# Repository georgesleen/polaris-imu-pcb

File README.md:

# Polaris IMU PCB

## Images

## Drawings

## Ordering

When ordering this PCB, please tag the commit that you used and create a release on GitHub with the appropriate revision number.

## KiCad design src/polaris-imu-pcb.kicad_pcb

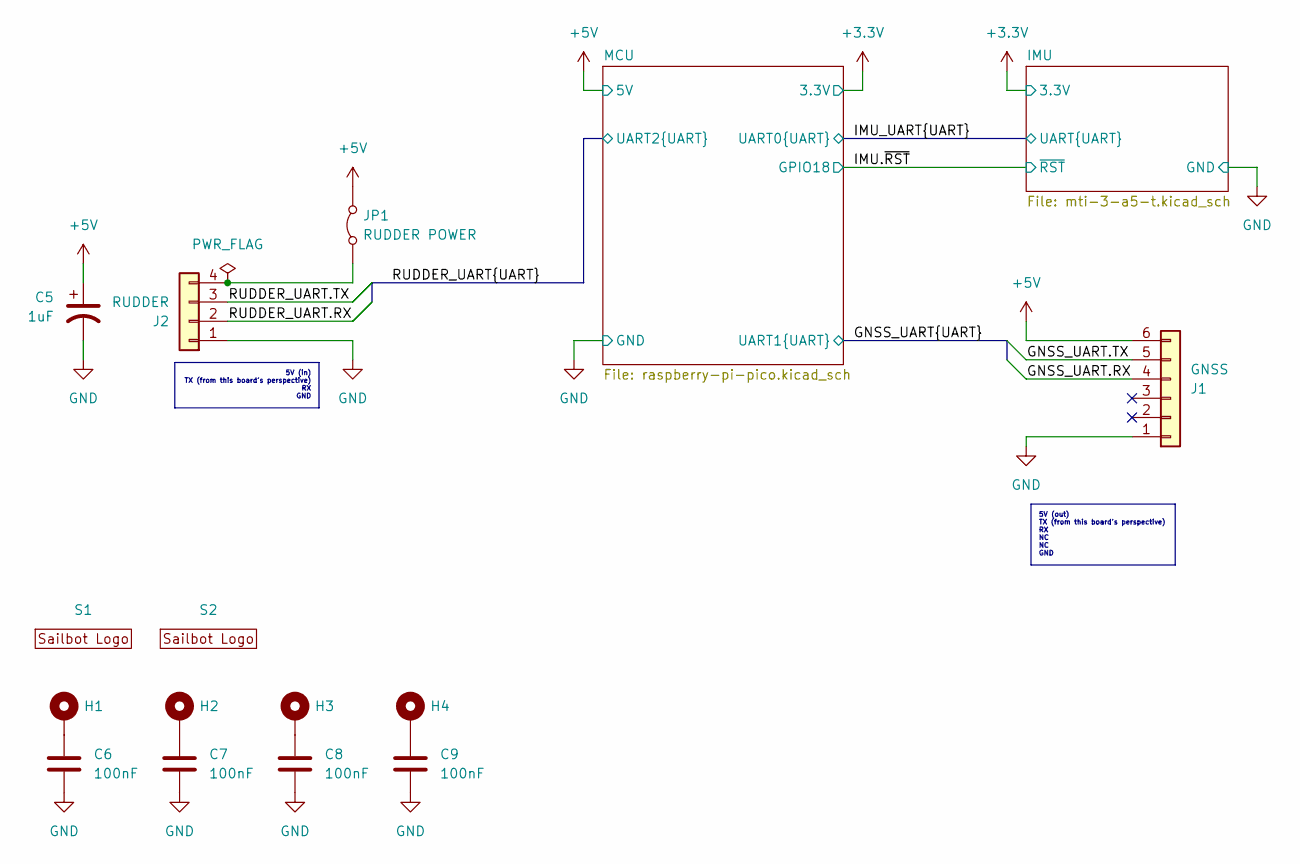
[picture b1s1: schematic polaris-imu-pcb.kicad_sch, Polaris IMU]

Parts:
C5: 1uF; CP_Radial_D5.0mm_P2.00mm
C6, C7, C8, C9: 100nF; C_Disc_D3.0mm_W2.0mm_P2.50mm
H1, H2, H3, H4: MountingHole_Pad; MountingHole_3.2mm_M3_Pad
J1: GNSS; JST_XH_S6B-XH-A-1_1x06_P2.50mm_Horizontal; MPN S6B-XH-A-1(LF)(SN); LCSC ID C265069
J2: RUDDER; JST_XH_S4B-XH-A-1_1x04_P2.50mm_Horizontal; MPN S4B-XH-A-1(LF)(SN); LCSC ID C163037
JP1: RUDDER POWER; TestPoint_2Pads_Pitch2.54mm_Drill0.8mm
S1: Logo; UBC_Sailbot_Logo_Silk
S2: Logo; UBC_Sailbot_Logo_Huge

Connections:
/+5V: C5.1, J1.6, JP1.2 (B); also elsewhere on the board
/GND: C5.2, C6.2, C7.2, C8.2, C9.2, J1.1, J2.1; also elsewhere on the board
/GNSS_UART.RX: J1.4; also elsewhere on the board
/GNSS_UART.TX: J1.5; also elsewhere on the board
/RUDDER_UART.RX: J2.2; also elsewhere on the board
/RUDDER_UART.TX: J2.3; also elsewhere on the board
unnamed: C6.1, H1.1 (1_1)
unnamed: C7.1, H2.1 (1_1)
unnamed: C8.1, H3.1 (1_1)
unnamed: C9.1, H4.1 (1_1)
unnamed: J2.4, JP1.1 (A)

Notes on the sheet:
5V (out) TX (from this board's perspective) RX NC NC GND
5V (in) TX (from this board's perspective) RX GND

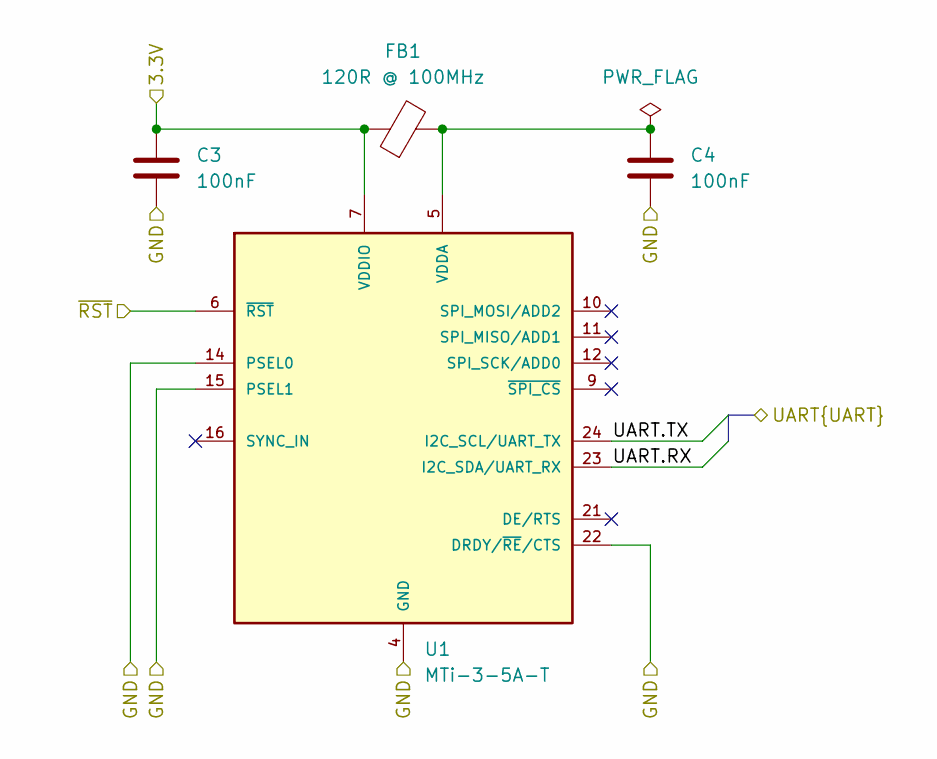
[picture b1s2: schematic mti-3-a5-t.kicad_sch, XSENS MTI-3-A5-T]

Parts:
C3, C4: 100nF; C_Disc_D3.0mm_W2.0mm_P2.50mm
FB1: 120R @ 100MHz; L_0603_1608Metric; MPN BLM18KG121TN1D; LCSC ID C85831
U1: MTi-3-5A-T; PLCC-28-AT; MPN MTi-3-5A-T

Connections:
/+3.3V: C3.1, FB1.1, U1.7 (VDDIO); also elsewhere on the board
/GND: C3.2, C4.2, U1.4 (GND), U1.8 (GND), U1.13 (GND), U1.14 (PSEL0), U1.15 (PSEL1), U1.22 (DRDY/~RE/CTS), U1.25 (GND); also elsewhere on the board
/IMU.~RST: U1.6 (~RST); also elsewhere on the board
/IMU_UART.RX: U1.23 (I2C_SDA/UART_RX); also elsewhere on the board
/IMU_UART.TX: U1.24 (I2C_SCL/UART_TX); also elsewhere on the board
unnamed: C4.1, FB1.2, U1.5 (VDDA)

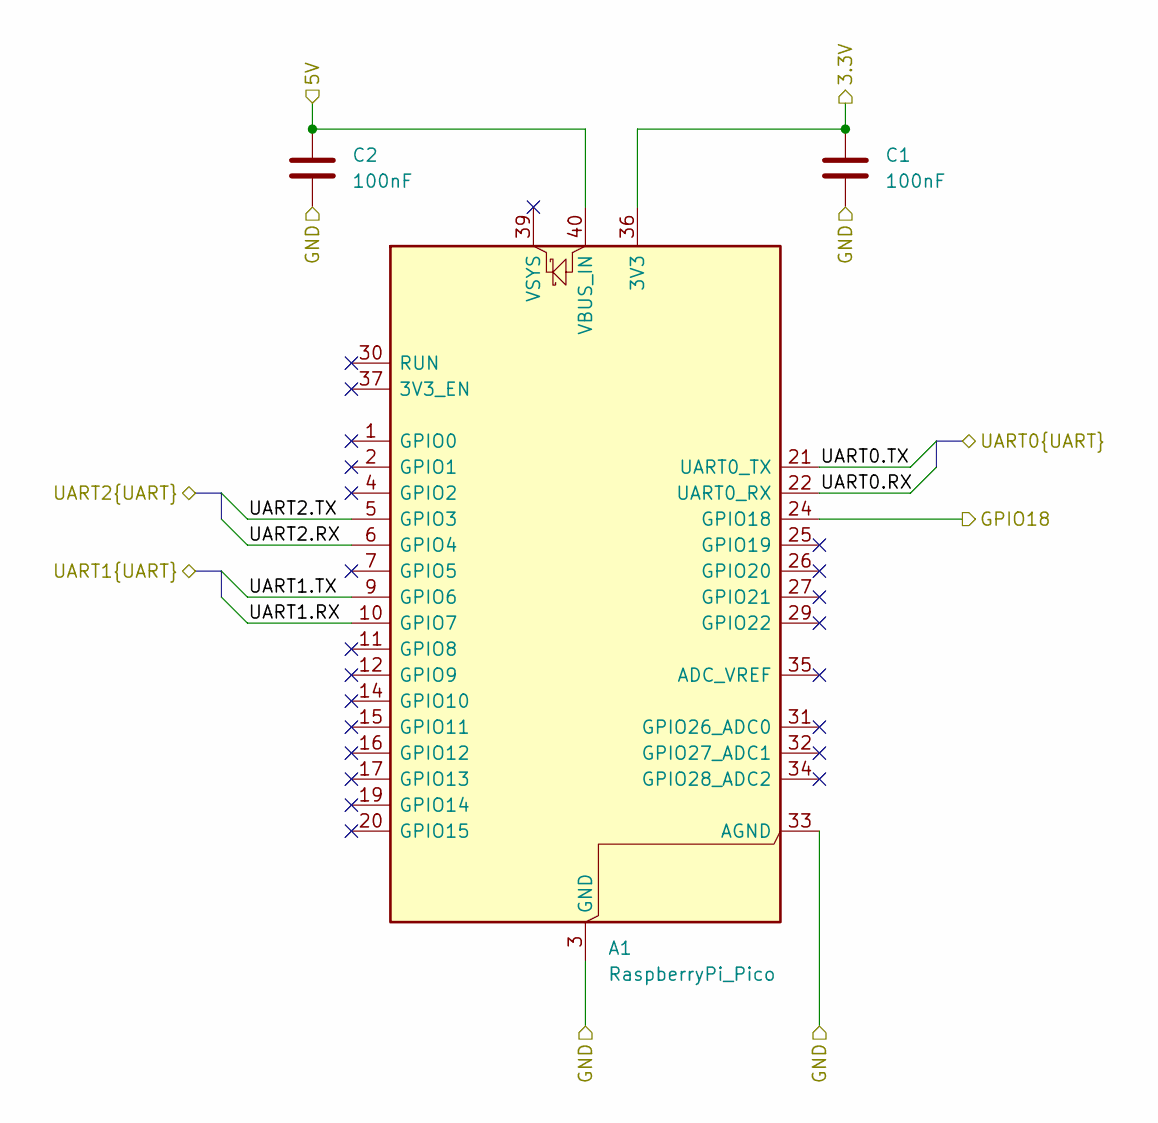
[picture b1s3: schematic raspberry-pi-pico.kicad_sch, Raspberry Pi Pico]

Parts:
A1: RaspberryPi_Pico; RaspberryPi_Pico_Common_SMD
C1, C2: 100nF; C_Disc_D3.0mm_W2.0mm_P2.50mm

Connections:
/+3.3V: A1.36 (3V3), C1.1; also elsewhere on the board
/+5V: A1.40 (VBUS_IN), C2.1; also elsewhere on the board
/GND: A1.3 (GND), A1.8 (GND), A1.13 (GND), A1.18 (GND), A1.23 (GND), A1.28 (GND), A1.33 (AGND), A1.38 (GND), C1.2, C2.2; also elsewhere on the board
/GNSS_UART.RX: A1.10 (GPIO7); also elsewhere on the board
/GNSS_UART.TX: A1.9 (GPIO6); also elsewhere on the board
/IMU.~RST: A1.24 (GPIO18); also elsewhere on the board
/IMU_UART.RX: A1.22 (UART0_RX); also elsewhere on the board
/IMU_UART.TX: A1.21 (UART0_TX); also elsewhere on the board
/RUDDER_UART.RX: A1.6 (GPIO4); also elsewhere on the board
/RUDDER_UART.TX: A1.5 (GPIO3); also elsewhere on the board

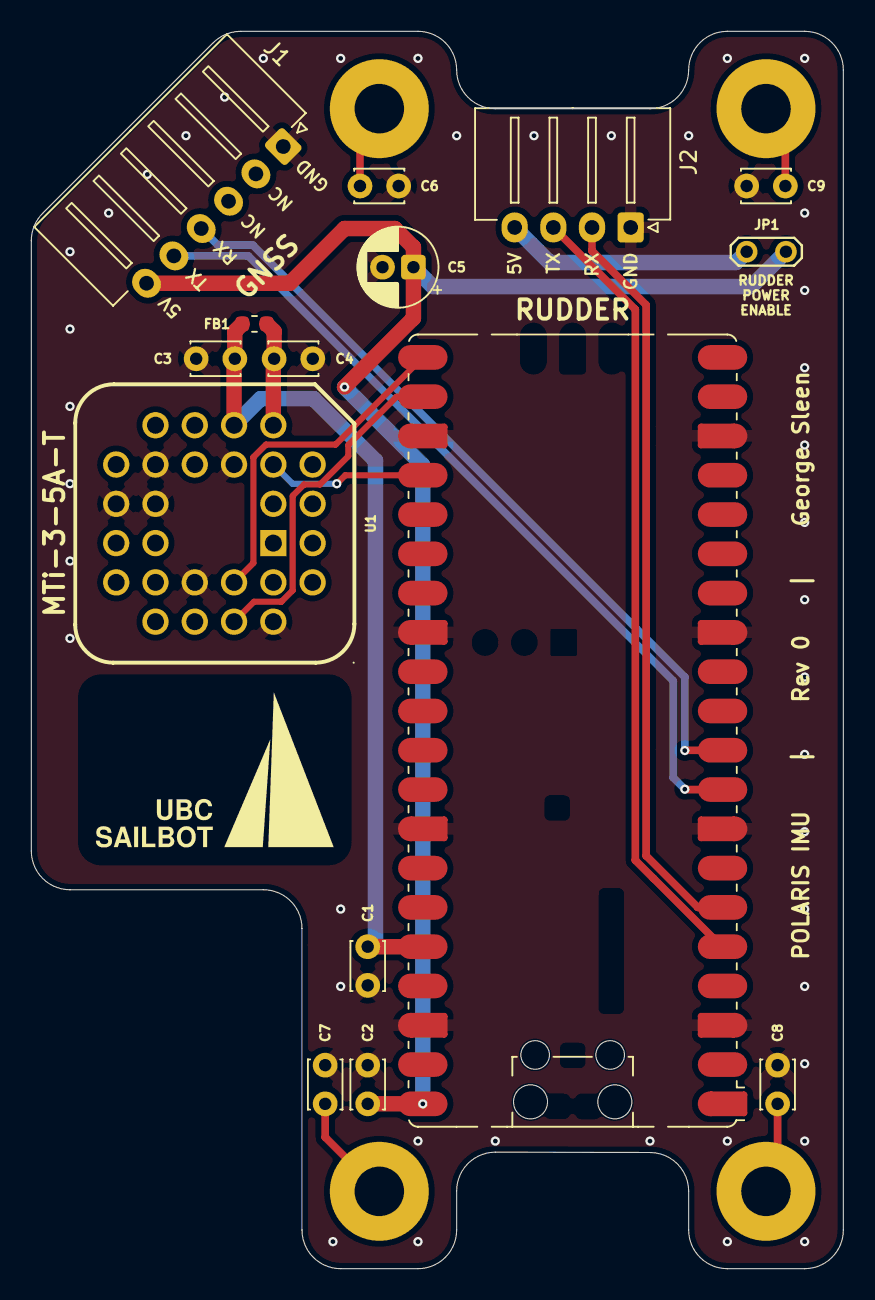
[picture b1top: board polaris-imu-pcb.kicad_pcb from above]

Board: 2 copper layers, 52.5 x 80.0 mm, 21 parts (1 on the bottom side), 16 nets.
